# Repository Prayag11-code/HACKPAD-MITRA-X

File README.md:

# HACKPAD-MITRA-X
Mitra X custom Hackpad. It a 9 key custom hackpad.
This was my first project in which i did pcb on kicad, and cad modelling in fusion 360. i had very difficulty but community helped me at its best. i learned how to make this. Now i will try making a key board at a large scale. Thanks Hackclub!!
Also Time, it took me atleast 10 hrs divided into 2 days, Day 1- 7 hrs , Day 2- 3hrs

## Bill of Materials (BOM)

| Part Name           | Quantity |
|---------------------|----------|
| PCB                 | 1        |
| Cherry MX Switch    | 9        |
| Keycaps             | 9        |
| Seeed XIAO RP2040   | 1        |
| Case                | 1        |
| M3x16 Bolt          | 4        |
| M3 Heatset          | 4        |
| SK6812 MINI LEDs    | 2        |

---

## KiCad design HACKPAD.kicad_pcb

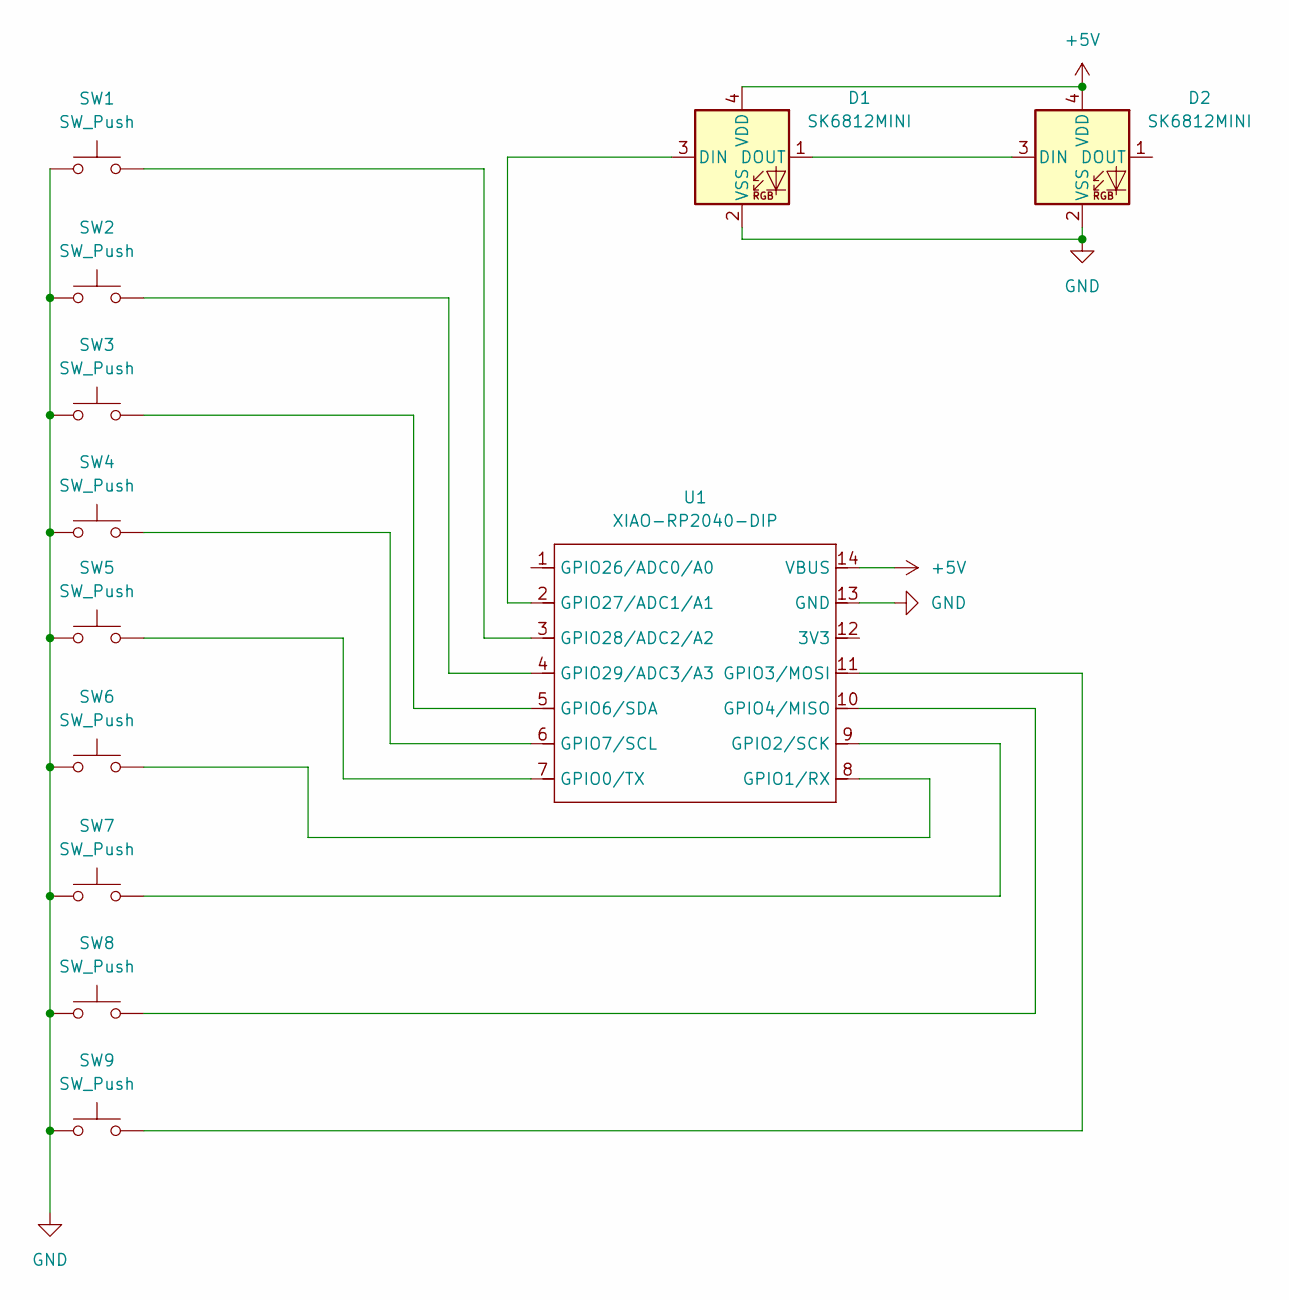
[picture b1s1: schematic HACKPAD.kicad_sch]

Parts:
D1, D2: SK6812MINI; LED_SK6812MINI_PLCC4_3.5x3.5mm_P1.75mm
SW1, SW2, SW3, SW4, SW5, SW6, SW7, SW8, SW9: SW_Push; SW_Cherry_MX_1.00u_PCB
U1: XIAO-RP2040-DIP

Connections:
+5V: D1.4 (VDD), D2.4 (VDD), U1.14 (VBUS)
GND: D1.2 (VSS), D2.2 (VSS), SW1.1, SW2.1, SW3.1, SW4.1, SW5.1, SW6.1, SW7.1, SW8.1, SW9.1, U1.13 (GND)
unnamed: D1.3 (DIN), U1.2 (GPIO27/ADC1/A1)
unnamed: D1.1 (DOUT), D2.3 (DIN)
unnamed: SW5.2, U1.7 (GPIO0/TX)
unnamed: SW6.2, U1.8 (GPIO1/RX)
unnamed: SW7.2, U1.9 (GPIO2/SCK)
unnamed: SW9.2, U1.11 (GPIO3/MOSI)
unnamed: SW8.2, U1.10 (GPIO4/MISO)
unnamed: SW3.2, U1.5 (GPIO6/SDA)
unnamed: SW4.2, U1.6 (GPIO7/SCL)
unnamed: SW1.2, U1.3 (GPIO28/ADC2/A2)
unnamed: SW2.2, U1.4 (GPIO29/ADC3/A3)

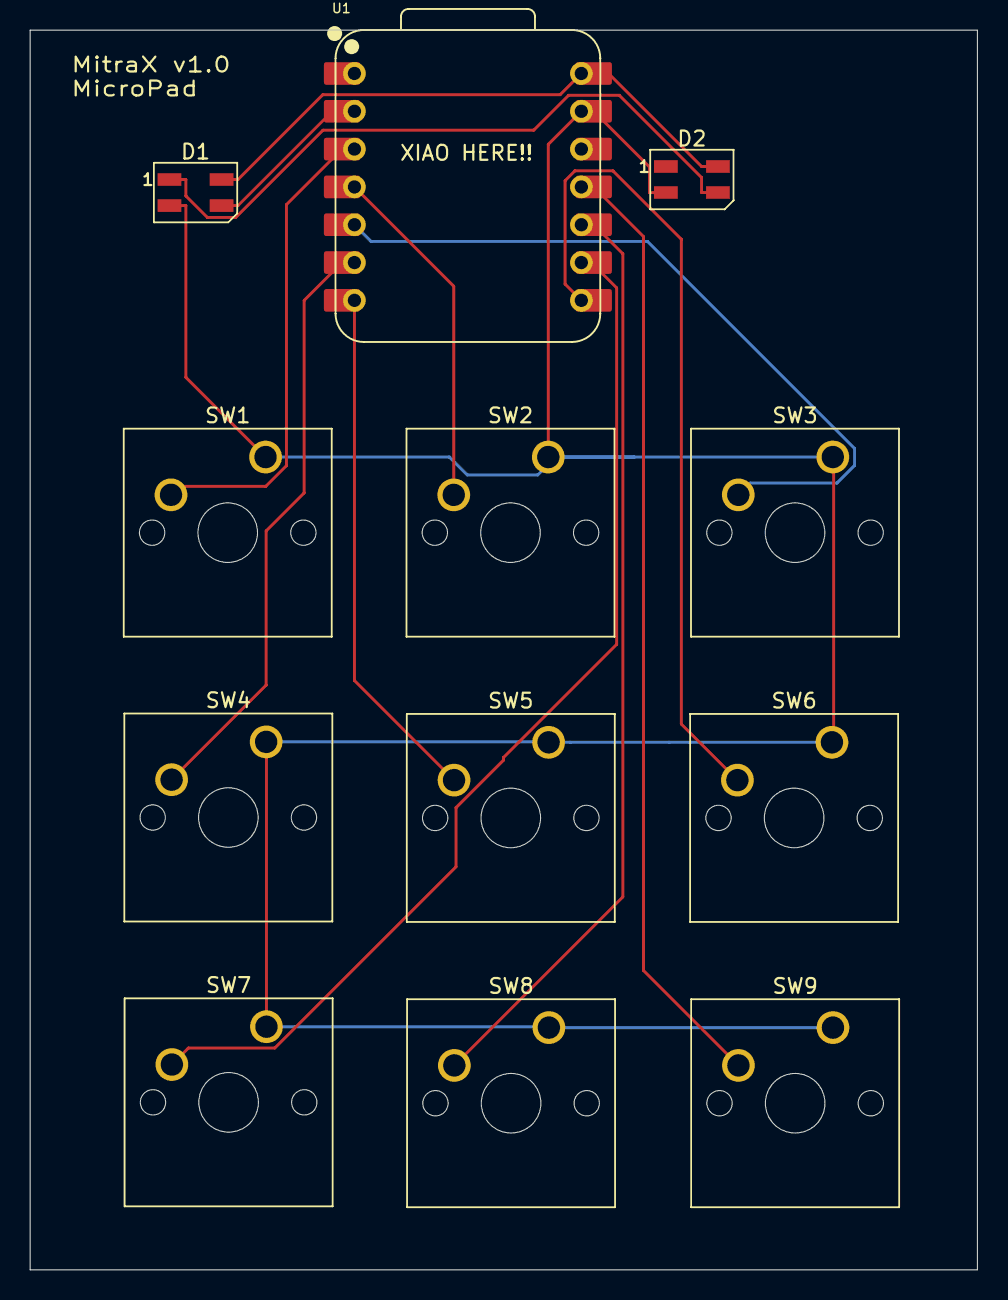
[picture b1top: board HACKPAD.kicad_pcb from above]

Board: 2 copper layers, 63.6 x 83.3 mm, 12 parts (0 on the bottom side), 13 nets.

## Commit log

2025-12-19 Create cad
2025-12-19 Create kicad
2025-12-19 Create images
2025-12-19 Create files
